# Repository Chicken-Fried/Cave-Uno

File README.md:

<h1 align="center">Cave Uno (Rev 1.0)</h1>

<p align="center">
  <b>English</b> | <a href="README_FR.md">Version Française 🇫🇷</a>
</p>

<p align="center">

</p>

**Cave Uno** is a next-generation open-source microcontroller development board engineered in Europe by **Cave Rover**. Conceived specifically for **engineering, electronics, and technical students**, as well as makers and university labs, Cave Uno is an upgraded, modern reinterpretation of the iconic **Arduino Uno Rev3**. 

It retains 100% mechanical, electrical, and shield compatibility with the Uno R3 form factor while addressing all classic limitations through modern silicon: **reversible USB-C with native plug-and-play driverless operation**, a high-efficiency synchronous buck converter, zero-voltage-drop ideal diode power OR-ing, a high-current 3.3V rail, switchable logic voltage, the extended peripherals of the **Microchip ATmega328PB**, and high-precision LiDAR vector silkscreen art celebrating the Ardèche river canyon.

---

## 🖼️ 3D Assembled Board Overview (KiCad Raytracing)

---

## 🎓 Tailored for Technical & Engineering Education

Traditional 8-bit educational boards often suffer from fragile power regulators, obsolete USB connectors, driver configuration hurdles, and single-bus bottlenecks. Cave Uno addresses these issues directly for students and educators:

* **100% Shield & Form-Factor Compatibility:** Fits existing Arduino Uno R3 shields, breadboard adapters, and lab enclosures without mechanical clashes.
* **Driverless Out-of-the-Box Experience:** No driver installers, unsigned driver warnings, or OS compatibility issues. Connect the USB-C cable and start coding immediately in the Arduino IDE.
* **Laboratory-Grade Power Protection:** Overvoltage-protected DC input, full TVS ESD suppression on USB data lines, and ideal diode reverse-current blocking prevent common lab wiring accidents.
* **Real-World Bus Architecture:** Teaches students modern multi-bus embedded design with Dual Hardware I2C (`Wire` / `Wire1`), Dual Hardware SPI, and Dual UART.
* **Flexible Logic Interfacing:** Eliminates messy resistor dividers and external level shifters when testing 3.3V sensors via the physical `SW1` VDD rail selector.

---

## ⚡ Highlights & Key Features

* **European Design & Heritage:** Designed and routed in Europe (France / Ardèche), featuring LiDAR elevation contours of the Pont d'Arc canyon and UNESCO Chauvet Cave.
* **Advanced ATmega328PB AVR Core @ 16 MHz:**
  * **Dual Hardware I2C (TWI0 & TWI1):** Independent simultaneous buses.
  * **Dual Hardware SPI (SPI0 & SPI1):** High-speed parallel display and SD logging.
  * **Dual USART (USART0 & USART1):** Dedicated serial monitor + hardware sensor telemetry.
  * **9 PWM Channels:** 3 extra output compare channels over standard 328P.
* **Modern Driverless USB-C Connectivity:** Powered by the **WCH CH9101R** USB-to-UART bridge with native OS CDC compliance across Windows 10/11, macOS, and Linux. No third-party drivers needed.
* **High-Efficiency 1.5A Synchronous Buck Converter:** Built with the **AP63205** step-down DC-DC regulator, accepting **7V to 18V** input with >90% efficiency.
* **Zero-Drop Power OR-ing:** Dual **LM66100** ideal diode controllers manage seamless switching between USB and external power with virtually zero voltage drop.
* **High-Current 600mA 3.3V Rail:** Dedicated **AP2112K-3.3** low-noise LDO powers modern power-hungry Wi-Fi (ESP8266/ESP32), radio (NRF24, LoRa), and sensor modules.
* **Selectable VDD Header (`SW1`):** A SPDT slide switch routes either **+5V** or **+3.3V** to the `J9` expansion bus.
* **Smart RGB NeoPixel LED:** Integrated addressable **WS2812B (2020)** RGB LED connected to GPIO `D23` (`PE0`) for user status and interactive tutorials.
* **Dedicated I2C_0 Port (`J7`):** Direct 4-pin connection (GND, 5V, SDA, SCL) for immediate sensor prototyping.
* **Dedicated UART Port (`J8`):** Direct 4-pin connection (RX0, TX0, GND, 5V) for serial modules and loggers.

---

## 📐 Pinout & Architecture

### Comprehensive Pin-by-Pin Mapping Table

Every single pin across all headers on the board is detailed below:

| Header | Pin # | Silk Label | MCU Port | TQFP-32 Pin | Default Function | Alternate & Special Functions |
|:---|:---:|:---|:---:|:---:|:---|:---|
| **J4** (Top Digital) | 10 | **SCL0** | PC5 | Pin 28 | Wire / TWI0 SCL | Analog Input A5, PCINT13 |
| | 9 | **SDA0** | PC4 | Pin 27 | Wire / TWI0 SDA | Analog Input A4, PCINT12 |
| | 8 | **AREF** | — | Pin 20 | AREF | Analog Voltage Reference Input |
| | 7 | **GND** | — | — | Ground | Digital Ground Reference |
| | 6 | **13** | PB5 | Pin 17 | Digital I/O | SCK0 (SPI0 Clock), Built-in LED L |
| | 5 | **12** | PB4 | Pin 16 | Digital I/O | MISO0 (SPI0 Master In / Slave Out) |
| | 4 | **~11** | PB3 | Pin 15 | Digital I/O | MOSI0 (SPI0 Master Out), PWM (Timer2 OCA) |
| | 3 | **~10** | PB2 | Pin 14 | Digital I/O | SS0 (SPI0 Slave Select), PWM (Timer1 OCB) |
| | 2 | **~9** | PB1 | Pin 13 | Digital I/O | PWM (Timer1 OCA) |
| | 1 | **8** | PB0 | Pin 12 | Digital I/O | CLKO / ICP1 (Timer1 Input Capture) |
| **J6** (Bottom Digital) | 8 | **7** | PD7 | Pin 11 | Digital I/O | AIN1 (Analog Comparator Negative In) |
| | 7 | **~6** | PD6 | Pin 10 | Digital I/O | AIN0 (Analog Comparator Positive In), PWM |
| | 6 | **~5** | PD5 | Pin 9 | Digital I/O | T1 (Timer1 Clock In), PWM (Timer0 OCB) |
| | 5 | **4** | PD4 | Pin 2 | Digital I/O | XCK0 (USART0 Clock), T0 |
| | 4 | **~3** | PD3 | Pin 1 | Digital I/O | INT1 (External Interrupt 1), PWM |
| | 3 | **2** | PD2 | Pin 32 | Digital I/O | INT0 (External Interrupt 0) |
| | 2 | **TX → 1** | PD1 | Pin 31 | UART TX0 | USART0 Asynchronous Transmit |
| | 1 | **RX ← 0** | PD0 | Pin 30 | UART RX0 | USART0 Asynchronous Receive |
| **J5** (Power) | 1 | **NC** | — | — | Not Connected | Uncommitted pin |
| | 2 | **IOREF** | — | — | +5.0V | Shield Logic Reference Voltage |
| | 3 | **RESET** | PC6 | Pin 29 | Active-Low Reset | Target MCU hardware reset |
| | 4 | **3.3V** | — | — | +3.3V Regulated | AP2112K LDO Output (600mA continuous) |
| | 5 | **5V** | — | — | +5.0V Regulated | AP63205 Buck / USB VBUS (1.5A max) |
| | 6 | **GND** | — | — | Ground | System Power Ground |
| | 7 | **GND** | — | — | Ground | System Power Ground |
| | 8 | **VIN** | — | — | Raw Input (7V–18V) | Power input from 5.5x2.1mm DC Barrel Jack |
| **J2** (Analog) | 1 | **A0** | PC0 | Pin 23 | Analog Input 0 | ADC Channel 0, PCINT8 |
| | 2 | **A1** | PC1 | Pin 24 | Analog Input 1 | ADC Channel 1, PCINT9 |
| | 3 | **A2** | PC2 | Pin 25 | Analog Input 2 | ADC Channel 2, PCINT10 |
| | 4 | **A3** | PC3 | Pin 26 | Analog Input 3 | ADC Channel 3, PCINT11 |
| | 5 | **A4** | PC4 | Pin 27 | Analog Input 4 | ADC Channel 4 / Wire TWI0 SDA |
| | 6 | **A5** | PC5 | Pin 28 | Analog Input 5 | ADC Channel 5 / Wire TWI0 SCL |
| **J3** (Extra I/O Header) | 1 | **SDA1** | PE0 | Pin 25 | Wire1 / TWI1 SDA | GPIO D23, WS2812B RGB DIN, RXD1 |
| | 2 | **SCL1** | PE1 | Pin 26 | Wire1 / TWI1 SCL | GPIO D24, MISO1 (SPI1), TXD1 |
| | 3 | **A6** | PE2 | Pin 19 | Analog Input 6 | ADC Channel 6, SS1 (SPI1 Slave Select) |
| | 4 | **A7** | PE3 | Pin 22 | Analog Input 7 | ADC Channel 7, MOSI1 (SPI1 Master Out) |
| **J7** (Dedicated I2C_0) | 1 | **GND** | — | — | Ground | Ground reference for I2C modules |
| | 2 | **5V** | — | — | +5.0V Regulated | 5V power supply rail for I2C sensors |
| | 3 | **SDA0** | PC4 | Pin 27 | Wire / TWI0 SDA | Primary I2C bus serial data |
| | 4 | **SCL0** | PC5 | Pin 28 | Wire / TWI0 SCL | Primary I2C bus serial clock |
| **J8** (Dedicated UART_0) | 1 | **D0** | PD0 | Pin 30 | UART RX0 | Hardware serial receive |
| | 2 | **D1** | PD1 | Pin 31 | UART TX0 | Hardware serial transmit |
| | 3 | **GND** | — | — | Ground | Serial ground reference |
| | 4 | **5V** | — | — | +5.0V Regulated | 5V power supply rail for serial modules |
| **J9** (Switchable VDD) | 1 | **VDD** | — | — | Rail Output 1 | Selected via SW1 (5V or 3.3V) |
| | 2 | **VDD** | — | — | Rail Output 2 | Selected via SW1 (5V or 3.3V) |
| | 3 | **VDD** | — | — | Rail Output 3 | Selected via SW1 (5V or 3.3V) |
| | 4 | **VDD** | — | — | Rail Output 4 | Selected via SW1 (5V or 3.3V) |
| **J10** (Extra GND Bus) | 1 | **GND** | — | — | Ground Pin 1 | System solid ground return |
| | 2 | **GND** | — | — | Ground Pin 2 | System solid ground return |
| | 3 | **GND** | — | — | Ground Pin 3 | System solid ground return |
| | 4 | **GND** | — | — | Ground Pin 4 | System solid ground return |
| **J1** (AVR ICSP Header) | 1 | **5V** | — | — | +5.0V Regulated | Target power during ISP programming |
| | 2 | **MOSI0** | PB3 | Pin 15 | SPI0 MOSI | In-System Programming Data In |
| | 3 | **MISO0** | PB4 | Pin 16 | SPI0 MISO | In-System Programming Data Out |
| | 4 | **SCK0** | PB5 | Pin 17 | SPI0 SCK | In-System Programming Clock |
| | 5 | **RESET** | PC6 | Pin 29 | Active-Low Reset | Target MCU hardware reset control |
| | 6 | **GND** | — | — | Ground | Programmer ground reference |

---

## 🔬 Hardware Diagnostic & Lab Test Points (`TP1` – `TP15`)

To facilitate oscilloscope probing, multimeter diagnostics, and hands-on electronics lab exercises, the Cave Uno integrates **15 surface-mount test pads** (Ø 1.0 mm ENIG gold pads on `F.Cu`):

| Test Point | Silkscreen / Value | Schematic Net | Nominal Signal / Voltage | Diagnostic & Laboratory Purpose |
|:---:|:---:|:---|:---:|:---|
| **TP1** | `USBVCC` | `USBVCC` | +5.0V DC | Raw USB-C $V_{BUS}$ input (upstream of ideal diode `U3`) |
| **TP2** | `VOUT` | `VOUT` | +5.0V DC | Regulated output of the `U4` (`AP63205`) synchronous buck converter (upstream of ideal diode `U2`) |
| **TP3** | `+5V` | `+5V` | +5.0V DC | Main system `+5V` rail (downstream of the dual `LM66100` ideal diode OR-ing stage) |
| **TP4** | `CE` | `Net-(U2-ST)` | Logic Signal | Cross-coupled Status / Chip-Enable (`ST`/`CE`) handshaking line between ideal diodes `U2` and `U3` |
| **TP5** | `VCC` | `VCC` | 7V – 18V DC | Reverse-polarity protected DC input (downstream of protection diode `D1`, feeding buck converter `U4`) |
| **TP6** | `VIN` | `Net-(D1-A)` | 7V – 18V DC | Raw external DC barrel jack (`U1`) input voltage (upstream of protection diode `D1`) |
| **TP7** | `RX` | `D0` | 5V TTL UART | Primary hardware UART receive line (`RX0` / `PD0`) between `CH9101R` and `ATmega328PB` |
| **TP8** | `TX` | `D1` | 5V TTL UART | Primary hardware UART transmit line (`TX0` / `PD1`) between `ATmega328PB` and `CH9101R` |
| **TP9** | `GND` | `GND` | 0V (Ground) | Reference ground probe pad (Power / Analog zone) for oscilloscope ground clips |
| **TP10** | `GND` | `GND` | 0V (Ground) | Reference ground probe pad (USB / Digital zone) for oscilloscope ground clips |
| **TP11** | `+3.3V` | `+3.3V` | +3.3V DC | Low-noise +3.3V LDO output from `U7` (`AP2112K-3.3`, 600 mA max) |
| **TP12** | `VDD` | `VDD` | +5.0V or +3.3V | Switchable logic power bus voltage selected via slide switch `SW1` |
| **TP13** | `RESET` | `RESET` | +5.0V (Active-Low) | Hardware MCU Reset line (`PC6`) & DTR auto-reset capacitive pulse observation point |
| **TP14** | `RX_LED` | `RX_LED` | Active-Low | USB-UART (`U6` `CH9101R`) serial RX traffic LED drive signal |
| **TP15** | `TX_LED` | `TX_LED` | Active-Low | USB-UART (`U6` `CH9101R`) serial TX traffic LED drive signal |

---

## 🛠️ Software Setup & Toolchain

The **Cave Uno** is 100% plug-and-play with the Arduino IDE, PlatformIO, VS Code, and AVR-GCC.

### 1. Arduino IDE Board Manager (MiniCore)

Because the ATmega328PB contains hardware peripherals beyond the legacy ATmega328P, install the **MiniCore** core package:

1. Open **Arduino IDE**, navigate to **File → Preferences**.
2. Add the following URL to **Additional Boards Manager URLs**:
   ```
   https://mcudude.github.io/MiniCore/package_MCUdude_MiniCore_index.json
   ```
3. Open **Tools → Board → Boards Manager...**, search for `MiniCore` by MCUdude, and click **Install**.
4. Configure your board settings under the **Tools** menu:
   * **Board:** `ATmega328`
   * **Variant:** `328PB`
   * **Clock:** `External 16 MHz`
   * **BOD:** `2.7V` (or `4.3V` for strict 5V operation)
   * **Compiler LTO:** `Enabled`
   * **Port:** Select the detected CH9101 USB Serial Port.

---

### 2. Code Examples

#### Dual Independent I2C Buses
```cpp
#include <Wire.h>

void setup() {
  Serial.begin(115200);
  
  // Primary I2C bus (PC4/PC5 - Pins A4/A5 and Header J7)
  Wire.begin();
  
  // Secondary I2C bus (PE0/PE1 - Header J3)
  Wire1.begin();
  
  Serial.println(F("Cave Uno Dual I2C Initialized!"));
}

void loop() {
  // Query OLED display on primary bus
  Wire.beginTransmission(0x3C);
  // ...
  Wire.endTransmission();

  // Query sensor on secondary bus without address conflict
  Wire1.beginTransmission(0x68);
  // ...
  Wire1.endTransmission();
  
  delay(1000);
}
```

#### On-Board WS2812B Smart RGB LED (`D23`)
```cpp
#include <Adafruit_NeoPixel.h>

#define RGB_PIN   23  // PE0 / D23
#define NUMPIXELS 1

Adafruit_NeoPixel statusLed(NUMPIXELS, RGB_PIN, NEO_GRB + NEO_KHZ800);

void setup() {
  statusLed.begin();
  statusLed.setBrightness(40);
}

void loop() {
  // Orange pulsing heartbeat (Cave Rover theme)
  statusLed.setPixelColor(0, statusLed.Color(249, 115, 22));
  statusLed.show();
  delay(800);
  
  statusLed.setPixelColor(0, statusLed.Color(0, 0, 0));
  statusLed.show();
  delay(200);
}
```

---

## ⚙️ Electrical Specifications

| Parameter | Minimum | Typical | Maximum | Unit | Notes |
|:---|:---:|:---:|:---:|:---:|:---|
| **Input Voltage ($V_{IN}$ DC Jack)** | 7.0 | 9.0 – 12.0 | 18.0 | V | 5.5 × 2.1mm center-positive |
| **USB Input ($V_{BUS}$)** | 4.75 | 5.0 | 5.25 | V | USB Type-C connector |
| **Operating Voltage ($V_{CC}$)** | 4.90 | 5.0 | 5.10 | V | Internal 5V system rail |
| **Switchable Rail ($V_{DD}$)** | — | 3.3 or 5.0 | — | V | Selected via `SW1` |
| **AP63205 Buck Max Current** | — | — | 1.5 | A | High-efficiency buck converter |
| **AP2112K LDO 3.3V Max Current**| — | — | 600 | mA | Ultra-low noise ($V_{DROP} = 250\,\text{mV}$) |
| **DC Current per I/O Pin** | — | — | 20.0 | mA | 40mA absolute maximum |
| **Total MCU Current** | — | — | 200.0 | mA | Combined $V_{CC}$ / GND limit |
| **MCU Clock Frequency** | — | 16.0 | — | MHz | External crystal $\pm 30\,\text{ppm}$ |

---

## 🏭 PCB Fabrication & Bare Board Preview

The PCB is authored in **KiCad 10** with 2-layer FR4 stackup and 100% clean DRC (0 errors, 0 unrouted nets).

* **Dimensions:** 68.6 mm × 53.4 mm (Arduino Uno R3 standard envelope).
* **Layer Stackup:**
  * Top: 1 oz (35 µm) Copper (`F.Cu`)
  * Core: 1.5 mm FR4 Core
  * Bottom: 1 oz (35 µm) Copper (`B.Cu`)
* **Recommended PCB Finish:** **ENIG** (Electroless Nickel Immersion Gold) for coplanar QFN-32 and TSOT-23 pads.
* **Soldermask:** Matte Black / Charcoal (`#1c1d21`).
* **Silkscreen:** High-definition White (`#f4f5f7`).
* **Clearance:** Min 0.15 mm / 0.15 mm (6/6 mil).

---

## 🗺️ European Engineering & Heritage

The back of the PCB features precision vector topographic contour lines derived from LiDAR scans of the **Pont d'Arc** natural canyon in Ardèche, France, adjacent to the prehistoric **Chauvet Cave** (UNESCO World Heritage Site).

* **Coordinates:** $44^{\circ}\,23'\,15''\,\text{N},\ 04^{\circ}\,24'\,59''\,\text{E}$
* **Silkscreen Artwork:** Pure vector contours with solder-mask subtraction to preserve pristine gold pads.

---

## 📜 Key Silicon Bill of Materials

| Reference | Part Number | Package | Description |
|:---|:---|:---|:---|
| **U8** | ATmega328PB-MN / AU | QFN-32 (5×5mm) | 8-bit AVR Microcontroller @ 16 MHz |
| **U4** | AP63205WU-7 | TSOT-23-6 | 5V / 1.5A Synchronous Buck Converter |
| **U7** | AP2112K-3.3TRG1 | SOT-25-5 | 3.3V / 600mA Low-Dropout Regulator |
| **U2, U3** | LM66100DCKR | SC-70-6 | Ideal Diode Dual Power OR-ing Controllers |
| **U6** | CH9101R | QSOP-16 | Driverless USB 2.0 to UART Bridge |
| **U5** | USBLC6-2SC6 | SOT-23-6 | Dual TVS ESD Diode Array |
| **USB1** | GT-USB-7025 | USB-C SMD | Reversible USB Type-C Receptacle |
| **U1** | XDJK-0051-025 | THT Barrel Jack | 5.5 × 2.1mm DC Power Input Connector |
| **LED1** | WS2812B-2020-V6 | 2020 SMD | Smart Addressable RGB LED (`D23`) |
| **SW1** | K3-1296S-J1 | SMD Slide | SPDT 5V / 3.3V Rail Voltage Selector |
| **SW2** | 4-Pin SMD Tactile | 5.2×5.2mm | Active-Low Hardware Reset Switch |

---

## 📄 License & Attribution

* **Hardware Design:** Licensed under the [CERN-OHL-P v2](https://ohwr.org/cern_ohl_p_v2.txt) (CERN Open Hardware Licence - Permissive).
* **Documentation & Artwork:** Licensed under [Creative Commons Attribution-ShareAlike 4.0 International (CC BY-SA 4.0)](https://creativecommons.org/licenses/by-sa/4.0/).
* **Engineering & Design:** **Cave Rover** (Europe, 2026).

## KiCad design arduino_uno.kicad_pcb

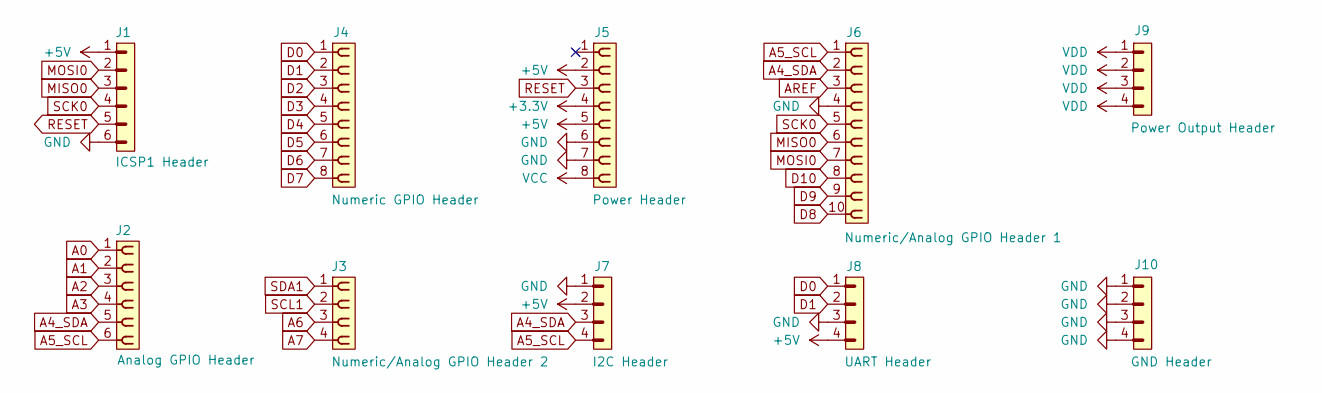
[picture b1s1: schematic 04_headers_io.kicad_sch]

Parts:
J1: ICSP1 Header; PinHeader_1x06_P2.54mm_Vertical; LCSC Part C505159
J2: Analog GPIO Header; PinSocket_1x06_P2.54mm_Vertical; LCSC Part C5224026
J3: Numeric/Analog GPIO Header 2; PinSocket_1x04_P2.54mm_Vertical; LCSC Part C5116530
J4: Numeric GPIO Header; PinSocket_1x08_P2.54mm_Vertical; LCSC Part C5224027
J5: Power Header; PinSocket_1x08_P2.54mm_Vertical; LCSC Part C5224027
J6: Numeric/Analog GPIO Header 1; PinSocket_1x10_P2.54mm_Vertical; LCSC Part C5116489
J7: I2C Header; PinHeader_1x04_P2.54mm_Vertical; LCSC Part C589358
J8: UART Header; PinHeader_1x04_P2.54mm_Vertical; LCSC Part C589358
J9: Power Output Header; PinHeader_1x04_P2.54mm_Vertical; LCSC Part C41425294
J10: GND Header; PinHeader_1x04_P2.54mm_Vertical; LCSC Part C42391438

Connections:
+3.3V: J5.4; also elsewhere on the board
+5V: J1.1, J5.2, J5.5, J7.2, J8.4; also elsewhere on the board
A0: J2.1; also elsewhere on the board
A1: J2.2; also elsewhere on the board
A2: J2.3; also elsewhere on the board
A3: J2.4; also elsewhere on the board
A4_SDA: J2.5, J6.2, J7.3; also elsewhere on the board
A5_SCL: J2.6, J6.1, J7.4; also elsewhere on the board
A6: J3.3; also elsewhere on the board
A7: J3.4; also elsewhere on the board
AREF: J6.3; also elsewhere on the board
D0: J4.1, J8.1; also elsewhere on the board
D1: J4.2, J8.2; also elsewhere on the board
D2: J4.3; also elsewhere on the board
D3: J4.4; also elsewhere on the board
D4: J4.5; also elsewhere on the board
D5: J4.6; also elsewhere on the board
D6: J4.7; also elsewhere on the board
D7: J4.8; also elsewhere on the board
D8: J6.10; also elsewhere on the board
D9: J6.9; also elsewhere on the board
D10: J6.8; also elsewhere on the board
GND: J1.6, J5.6, J5.7, J6.4, J7.1, J8.3, J10.1, J10.2, J10.3, J10.4; also elsewhere on the board
MISO0: J1.3, J6.6; also elsewhere on the board
MOSI0: J1.2, J6.7; also elsewhere on the board
RESET: J1.5, J5.3; also elsewhere on the board
SCK0: J1.4, J6.5; also elsewhere on the board
SCL1: J3.2; also elsewhere on the board
SDA1: J3.1; also elsewhere on the board
VCC: J5.8; also elsewhere on the board
VDD: J9.1, J9.2, J9.3, J9.4; also elsewhere on the board

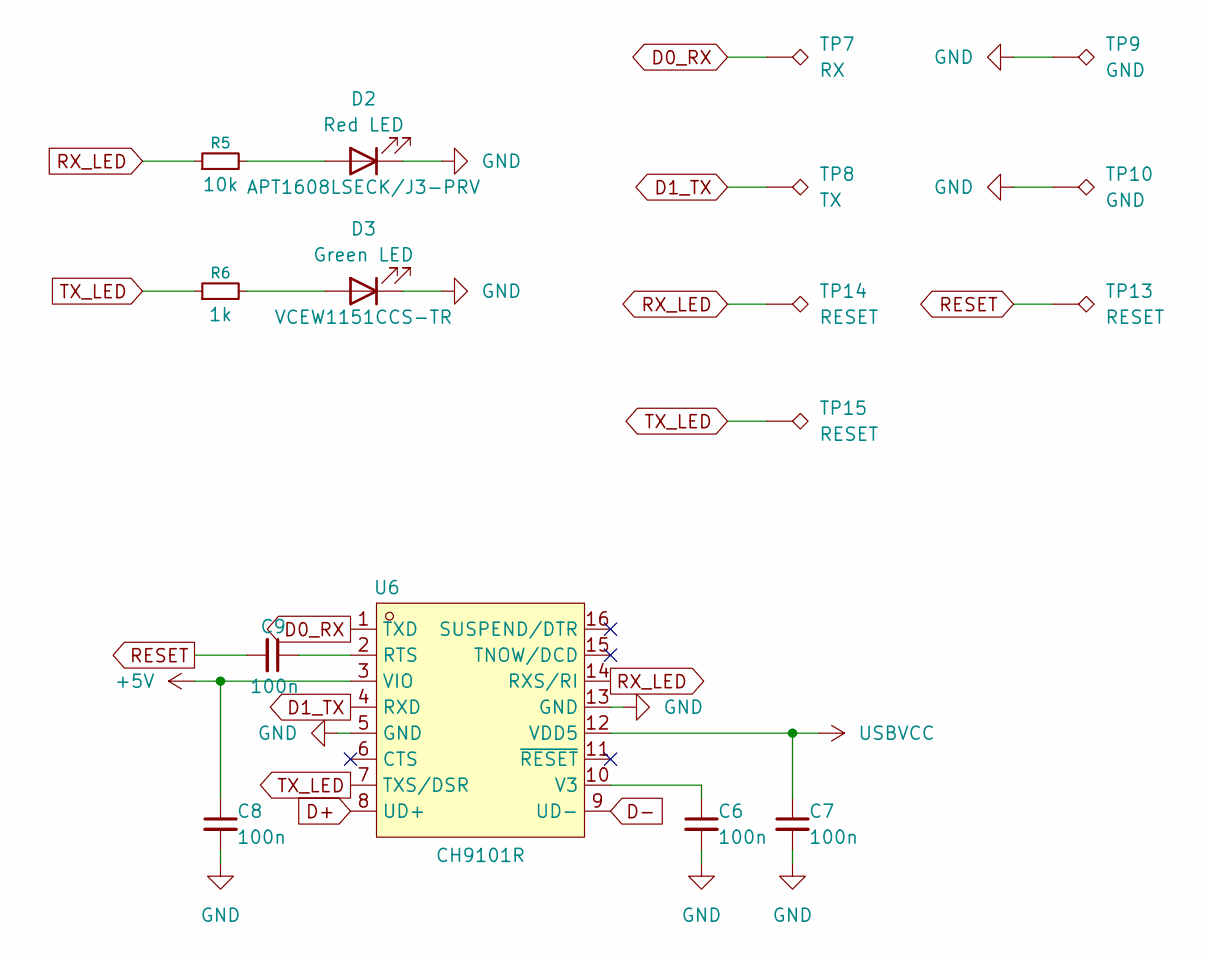
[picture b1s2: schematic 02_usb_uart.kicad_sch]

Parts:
C6, C7, C8, C9: 100n; C_0603_1608Metric; LCSC Part C346190
D2: Red LED; LED_0603_1608Metric; LCSC Part C5357909
D3: Green LED; LED_0603_1608Metric; LCSC Part C7410054
R5: 10k; R_0603_1608Metric; LCSC Part C191784
R6: 1k; R_0603_1608Metric; LCSC Part C191783
TP7: RX; TestPoint_Pad_D1.0mm
TP8: TX; TestPoint_Pad_D1.0mm
TP9, TP10: GND; TestPoint_Pad_D1.0mm
TP13, TP14, TP15: RESET; TestPoint_Pad_D1.0mm
U6: CH9101R; QSOP-16_L4.9-W3.9-P0.64-LS6.0-BL; MPN CH9101R; LCSC Part C5187520

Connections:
+5V: C8.1, U6.3 (VIO); also elsewhere on the board
D0: TP7.1 (1_1), U6.1 (TXD); also elsewhere on the board
D1: TP8.1 (1_1), U6.4 (RXD); also elsewhere on the board
D+: U6.8 (UD+); also elsewhere on the board
D-: U6.9 (UD-); also elsewhere on the board
GND: C6.2, C7.2, C8.2, D2.1 (K), D3.1 (K), TP9.1 (1_1), TP10.1 (1_1), U6.5 (GND), U6.13 (GND); also elsewhere on the board
unnamed: D2.2 (A), R5.2
unnamed: D3.2 (A), R6.2
unnamed: C9.1, U6.2 (RTS)
unnamed: C6.1, U6.10 (V3)
RESET: C9.2, TP13.1 (1_1); also elsewhere on the board
RX_LED: R5.1, TP14.1 (1_1), U6.14 (RXS/RI)
TX_LED: R6.1, TP15.1 (1_1), U6.7 (TXS/DSR)
USBVCC: C7.1, U6.12 (VDD5); also elsewhere on the board

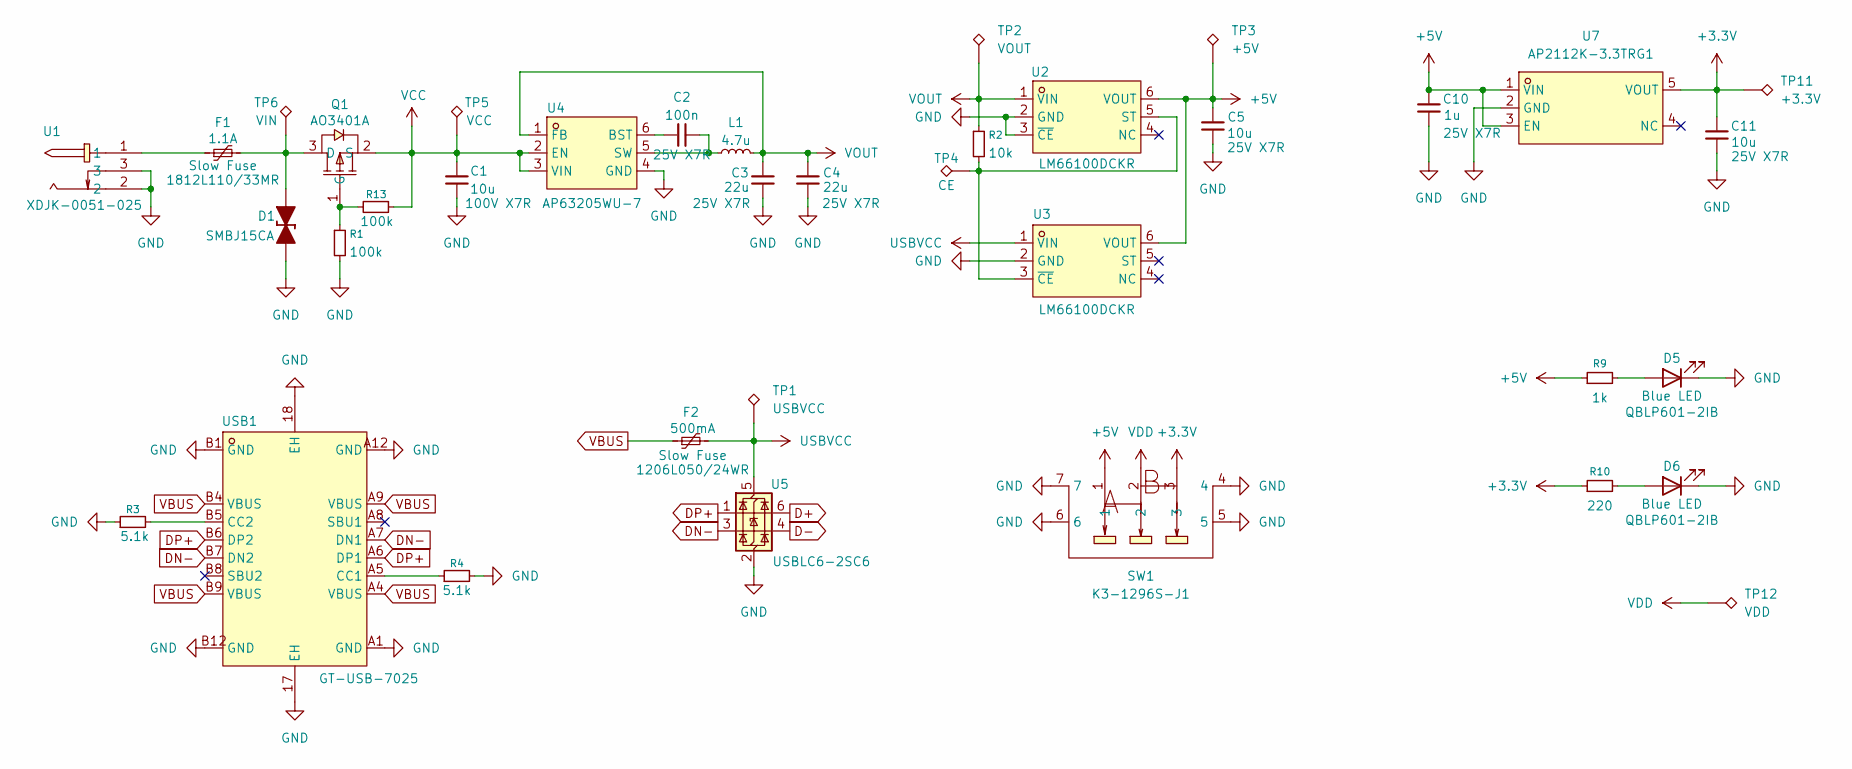
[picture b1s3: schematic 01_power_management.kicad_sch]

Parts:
C1: 10u; C_1206_3216Metric; LCSC Part C89632
C2: 100n; C_0603_1608Metric; LCSC Part C346190
C3, C4: 22u; C_1210_3225Metric; LCSC Part C2918511
C5, C11: 10u; C_0805_2012Metric; LCSC Part C3039694
C10: 1u; C_0603_1608Metric; LCSC Part C469535
D1: SMBJ15CA; SMB_L4.6-W3.6-LS5.3-BI; LCSC Part C78809
D5, D6: Blue LED; LED_0603_1608Metric; LCSC Part C6629785
F1: 1.1A; F1812; LCSC Part C142747
F2: 500mA; Fuse_1206_3216Metric; LCSC Part C2154056
L1: 4.7u; L_Sunlord_SWPA4030S; LCSC Part C57269
Q1: AO3401A; SOT-23_L2.9-W1.3-P1.90-LS2.4-BR; MPN AO3401A; LCSC Part C15127
R1, R13: 100k; R_0603_1608Metric; LCSC Part C2988967
R2: 10k; R_0603_1608Metric; LCSC Part C191784
R3, R4: 5.1k; R_0603_1608Metric; LCSC Part C191166
R9: 1k; R_0603_1608Metric; LCSC Part C191783
R10: 220; R_0603_1608Metric; LCSC Part C2078042
SW1: K3-1296S-J1; SW-SMD_K3-1296S-J1; MPN K3-1296S-J1; LCSC Part C223848
TP1: USBVCC; TestPoint_Pad_D1.0mm
TP2: VOUT; TestPoint_Pad_D1.0mm
TP3: +5V; TestPoint_Pad_D1.0mm
TP4: CE; TestPoint_Pad_D1.0mm
TP5: VCC; TestPoint_Pad_D1.0mm
TP6: VIN; TestPoint_Pad_D1.0mm
TP11: +3.3V; TestPoint_Pad_D1.0mm
TP12: VDD; TestPoint_Pad_D1.0mm
U1: XDJK-0051-025; DC-IN-TH_XDJK-0051-025; MPN XDJK-0051-025; LCSC Part C7498153
U2, U3: LM66100DCKR; SC-70-6_L2.0-W1.3-P0.65-LS2.1-BL; MPN LM66100DCKR; LCSC Part C2869734
U4: AP63205WU-7; TSOT-23-6_L2.9-W1.6-P0.95-LS2.8-BL; MPN AP63205WU-7; LCSC Part C2071056
U5: USBLC6-2SC6; SOT-23-6; LCSC Part C7519
U7: AP2112K-3.3TRG1; SOT-25-5_L2.9-W1.6-P0.95-LS2.8-BL; MPN AP2112K-3.3TRG1; LCSC Part C51118
USB1: GT-USB-7025; TYPE-C-SMD_GT-USB-7025; MPN GT-USB-7025; LCSC Part C963213

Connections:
+3.3V: C11.1, R10.1, SW1.3, TP11.1 (1_1), U7.5 (VOUT); also elsewhere on the board
+5V: C5.1, C10.1, R9.1, SW1.1, TP3.1 (1_1), U2.6 (VOUT), U3.6 (VOUT), U7.1 (VIN), U7.3 (EN); also elsewhere on the board
D+: U5.6 (I/O1); also elsewhere on the board
D-: U5.4 (I/O2); also elsewhere on the board
DN-: U5.3 (I/O2), USB1.A7 (DN1), USB1.B7 (DN2)
DP+: U5.1 (I/O1), USB1.A6 (DP1), USB1.B6 (DP2)
GND: C1.2, C3.2, C4.2, C5.2, C10.2, C11.2, D1.1 (K), D5.1 (K), D6.1 (K), R1.2, R3.1, R4.2, SW1.4, SW1.5, SW1.6, SW1.7, U1.2, U1.3, U2.2 (GND), U2.3 (~CE), U3.2 (GND), U4.4 (GND), U5.2 (GND), U7.2 (GND), USB1.17 (EH), USB1.18 (EH), USB1.A1 (GND), USB1.A12 (GND), USB1.B1 (GND), USB1.B12 (GND); also elsewhere on the board
unnamed: D1.2 (A), F1.2, Q1.3 (D), TP6.1 (1_1)
unnamed: D5.2 (A), R9.2
unnamed: D6.2 (A), R10.2
unnamed: F1.1, U1.1
unnamed: Q1.1 (G), R1.1, R13.2
unnamed: R2.2, TP4.1 (1_1), U2.5 (ST), U3.3 (~CE)
unnamed: C2.1, U4.6 (BST)
unnamed: C2.2, L1.1, U4.5 (SW)
unnamed: R4.1, USB1.A5 (CC1)
unnamed: R3.2, USB1.B5 (CC2)
USBVCC: F2.2, TP1.1 (1_1), U3.1 (VIN), U5.5 (VBUS); also elsewhere on the board
VBUS: F2.1, USB1.A4 (VBUS), USB1.A9 (VBUS), USB1.B4 (VBUS), USB1.B9 (VBUS)
VCC: C1.1, Q1.2 (S), R13.1, TP5.1 (1_1), U4.2 (EN), U4.3 (VIN); also elsewhere on the board
VDD: SW1.2, TP12.1 (1_1); also elsewhere on the board
VOUT: C3.1, C4.1, L1.2, R2.1, TP2.1 (1_1), U2.1 (VIN), U4.1 (FB)

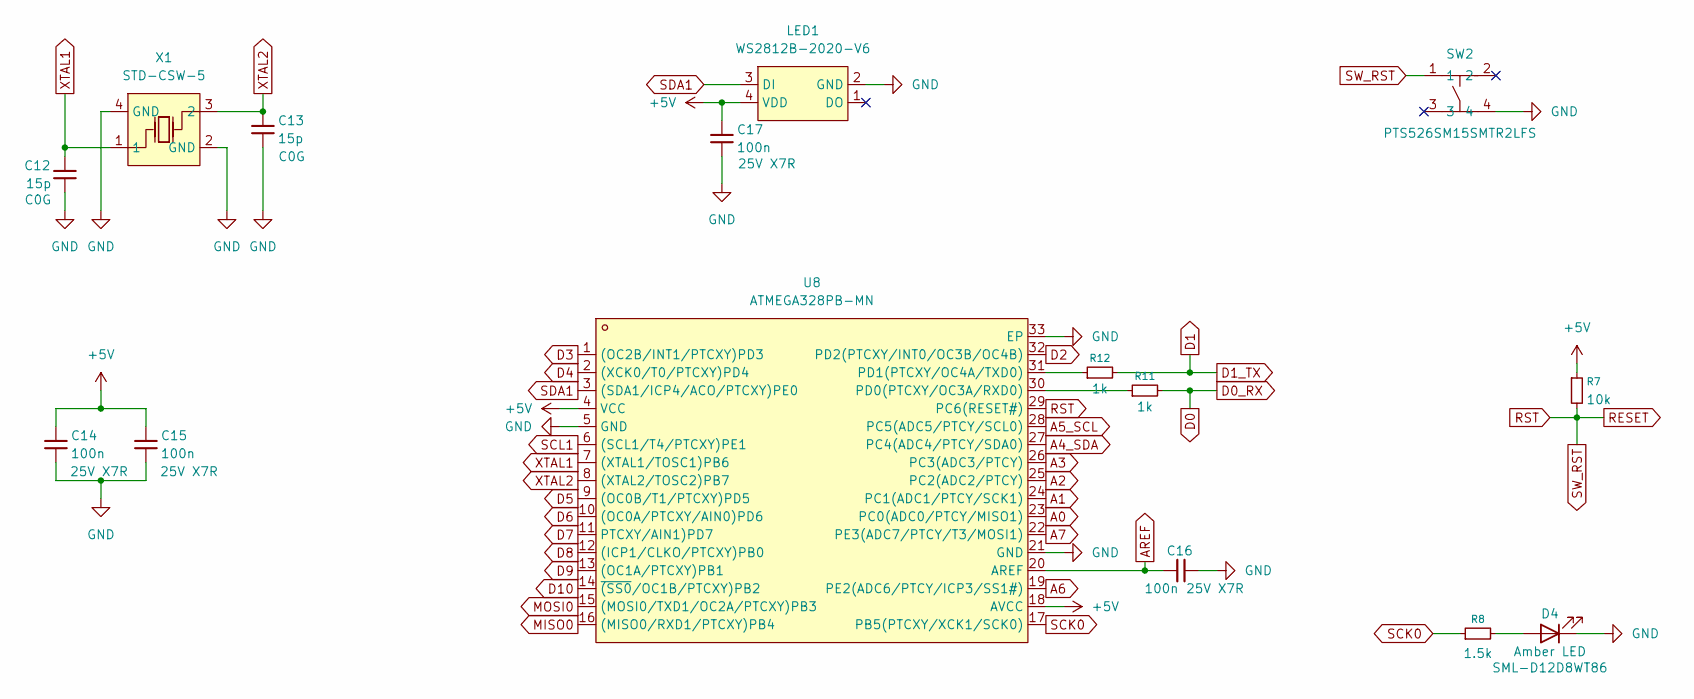
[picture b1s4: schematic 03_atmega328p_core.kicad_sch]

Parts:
C12, C13: 15p; C_0603_1608Metric; LCSC Part C597069
C14, C15, C16, C17: 100n; C_0603_1608Metric; LCSC Part C346190
D4: Amber LED; LED_0603_1608Metric; LCSC Part C510024
LED1: WS2812B-2020-V6; LED-SMD_4P-L2.2-W2.0-P1.00_WS2815C-2020-4P; MPN WS2812B-2020-V6; LCSC Part C52917434
R7: 10k; R_0603_1608Metric; LCSC Part C191784
R8: 1.5k; R_0603_1608Metric; LCSC Part C2989362
R11, R12: 1k; R_0603_1608Metric; LCSC Part C191783
SW2: PTS526SM15SMTR2LFS; SW-SMD_4P-L5.2-W5.2-P3.70-LS6.4; MPN PTS526SM15SMTR2LFS; LCSC Part C2689538
U8: ATMEGA328PB-MN; QFN-32_L5.0-W5.0-P0.50-TL-EP3.1; MPN ATMEGA328PB-MN; LCSC Part C1337164
X1: STD-CSW-5; CRYSTAL-SMD_4P-L2.5-W2.0-BL-A; MPN NX2520SA-16MHZ-STD-CSW-5; LCSC Part C280836

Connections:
+5V: C14.1, C15.1, C17.1, LED1.4 (VDD), R7.1, U8.4 (VCC), U8.18 (AVCC); also elsewhere on the board
A0: U8.23 (PC0(ADC0/PTCY/MISO1)); also elsewhere on the board
A1: U8.24 (PC1(ADC1/PTCY/SCK1)); also elsewhere on the board
A2: U8.25 (PC2(ADC2/PTCY)); also elsewhere on the board
A3: U8.26 (PC3(ADC3/PTCY)); also elsewhere on the board
A4_SDA: U8.27 (PC4(ADC4/PTCY/SDA0)); also elsewhere on the board
A5_SCL: U8.28 (PC5(ADC5/PTCY/SCL0)); also elsewhere on the board
A6: U8.19 (PE2(ADC6/PTCY/ICP3/SS1#)); also elsewhere on the board
A7: U8.22 (PE3(ADC7/PTCY/T3/MOSI1)); also elsewhere on the board
AREF: C16.1, U8.20 (AREF); also elsewhere on the board
D0: R11.2; also elsewhere on the board
D1: R12.2; also elsewhere on the board
D2: U8.32 (PD2(PTCXY/INT0/OC3B/OC4B)); also elsewhere on the board
D3: U8.1 ((OC2B/INT1/PTCXY)PD3); also elsewhere on the board
D4: U8.2 ((XCK0/T0/PTCXY)PD4); also elsewhere on the board
D5: U8.9 ((OC0B/T1/PTCXY)PD5); also elsewhere on the board
D6: U8.10 ((OC0A/PTCXY/AIN0)PD6); also elsewhere on the board
D7: U8.11 (PTCXY/AIN1)PD7); also elsewhere on the board
D8: U8.12 ((ICP1/CLKO/PTCXY)PB0); also elsewhere on the board
D9: U8.13 ((OC1A/PTCXY)PB1); also elsewhere on the board
D10: U8.14 (~(SS0/OC1B/PTCXY)PB2); also elsewhere on the board
GND: C12.2, C13.2, C14.2, C15.2, C16.2, C17.2, D4.1 (K), LED1.2 (GND), SW2.4, U8.5 (GND), U8.21 (GND), U8.33 (EP), X1.2 (GND), X1.4 (GND); also elsewhere on the board
MISO0: U8.16 ((MISO0/RXD1/PTCXY)PB4); also elsewhere on the board
MOSI0: U8.15 ((MOSI0/TXD1/OC2A/PTCXY)PB3); also elsewhere on the board
unnamed: D4.2 (A), R8.2
unnamed: R11.1, U8.30 (PD0(PTCXY/OC3A/RXD0))
unnamed: R12.1, U8.31 (PD1(PTCXY/OC4A/TXD0))
RESET: R7.2, SW2.1, U8.29 (PC6(RESET#)); also elsewhere on the board
SCK0: R8.1, U8.17 (PB5(PTCXY/XCK1/SCK0)); also elsewhere on the board
SCL1: U8.6 ((SCL1/T4/PTCXY)PE1); also elsewhere on the board
SDA1: LED1.3 (DI), U8.3 ((SDA1/ICP4/ACO/PTCXY)PE0); also elsewhere on the board
XTAL1: C12.1, U8.7 ((XTAL1/TOSC1)PB6), X1.1
XTAL2: C13.1, U8.8 ((XTAL2/TOSC2)PB7), X1.3 (2)

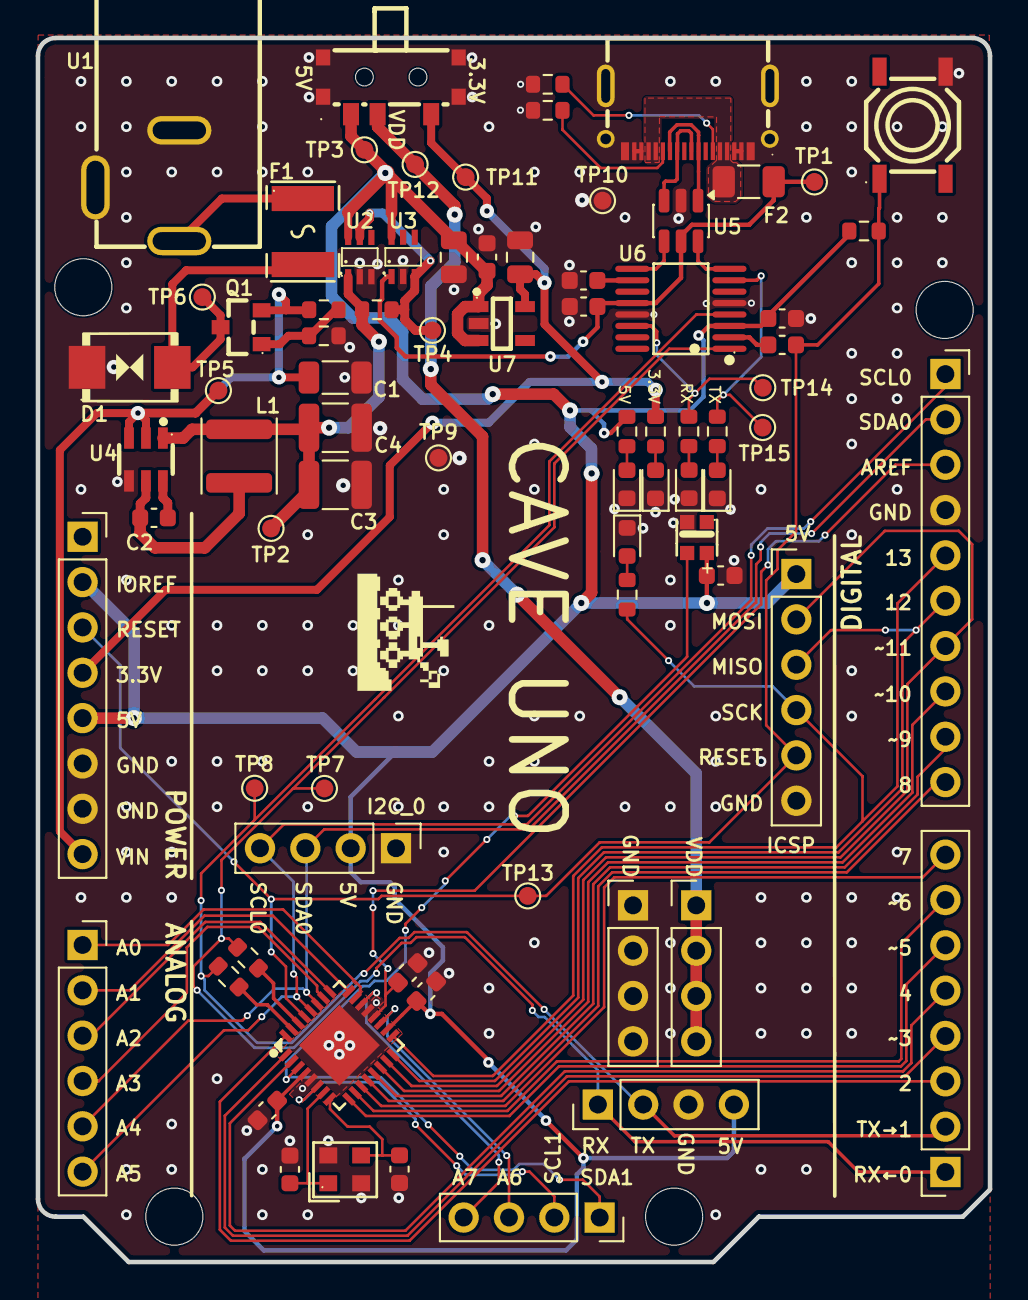
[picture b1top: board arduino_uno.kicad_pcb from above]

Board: 2 copper layers, 53.3 x 68.6 mm, 85 parts (1 on the bottom side), 59 nets.

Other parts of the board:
ART1: Artwork_Cave_Topo
LOGO**: Logo_CaveRover_F_SilkS; Logo_CaveRover
LOGO**#2: Logo_CaveRover_F_SilkS; Logo_CaveRover
UNK_HOLE_1, UNK_HOLE_1#2: dummyfp1
UNK_HOLE_2: dummyfp2
UNK_HOLE_3: dummyfp3

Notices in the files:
README.md:
Hardware License
